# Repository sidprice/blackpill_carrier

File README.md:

# blackpill_carrier

This PCB is to be used to make a stable Blackmagic Probe debugger when the platform is Blackpill, in particular the F411 blackpill.

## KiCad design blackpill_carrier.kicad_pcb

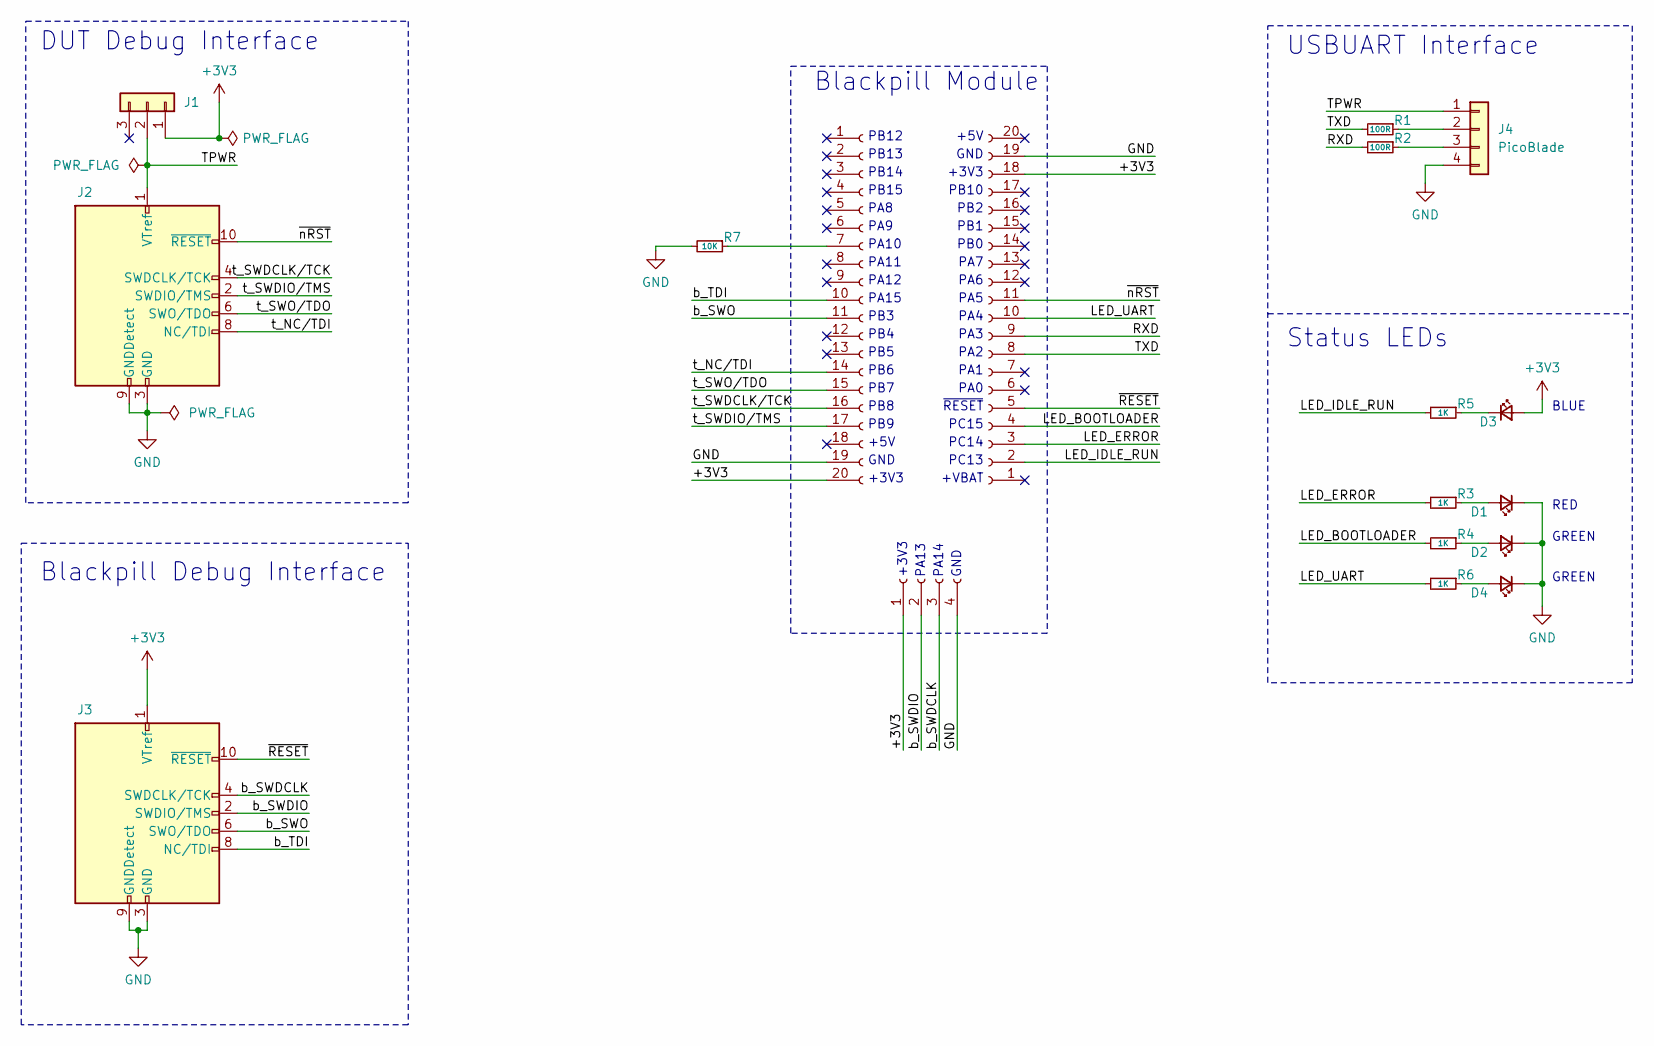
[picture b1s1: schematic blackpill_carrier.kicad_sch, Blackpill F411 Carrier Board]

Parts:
D1: LTSTC170KR; LTSTC170_LED_0805; LCSC C94868
D2, D4: LTSTC170KG; LTSTC170_LED_0805; LCSC C98221
D3: LTSTC170KB; LTSTC170_LED_0805; LCSC C98222
J1: M50-3630342; PinHeader_1x03_P1.27mm_Vertical_SMD_Pin1Right; LCSC C3336318
J2, J3: FTSH-105-01-F-DV-K-P-TR; PinHeader_2x05_P1.27mm_Vertical_SMD; Mouser 200-FTSH10501FDVKPTR
J4: PicoBlade; Molex_PicoBlade_53261-0471_1x04-1MP_P1.25mm_Horizontal; Mouser 538-53261-0471
J5, J6: B-2200S20P-A120; PinSocket_1x20_P2.54mm_Vertical; LCSC C124410
J7: B-2200S04P-A120; PinSocket_1x04_P2.54mm_Vertical; LCSC C124413
R1, R2: 100R; R_0603_1608Metric; LCSC C25201
R3, R4, R5, R6: 1K; R_0603_1608Metric; LCSC C25585
R7: 10K; R_0603_1608Metric; LCSC C15401

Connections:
+3V3: D3.2 (A), J1.1, J3.1 (VTref), J5.20, J6.18, J7.1
/LED_BOOTLOADER: J6.4, R4.2
/LED_ERROR: J6.3, R3.2
/LED_IDLE_RUN: J6.2, R5.2
/LED_UART: J6.10, R6.2
/RXD: J6.9, R2.2
/TPWR: J1.2, J2.1 (VTref), J4.1
/TXD: J6.8, R1.2
/b_SWDCLK: J3.4 (SWDCLK/TCK), J7.3
/b_SWDIO: J3.2 (SWDIO/TMS), J7.2
/b_SWO: J3.6 (SWO/TDO), J5.11
/b_TDI: J3.8 (NC/TDI), J5.10
/t_NC/TDI: J2.8 (NC/TDI), J5.14
/t_SWDCLK/TCK: J2.4 (SWDCLK/TCK), J5.16
/t_SWDIO/TMS: J2.2 (SWDIO/TMS), J5.17
/t_SWO/TDO: J2.6 (SWO/TDO), J5.15
/~RESET: J3.10 (~RESET), J6.5
/~nRST: J2.10 (~RESET), J6.11
GND: D1.1 (K), D2.1 (K), D4.1 (K), J2.3 (GND), J2.5 (GND), J2.9 (GNDDetect), J3.3 (GND), J3.5 (GND), J3.9 (GNDDetect), J4.4, J5.19, J6.19, J7.4, R7.2
unnamed: D1.2 (A), R3.1
unnamed: D2.2 (A), R4.1
unnamed: D3.1 (K), R5.1
unnamed: D4.2 (A), R6.1
unnamed: J4.2, R1.1
unnamed: J4.3, R2.1
unnamed: J5.7, R7.1

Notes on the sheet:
PB6
GND
PA4
PB3
PB2
USBUART Interface
PB12
PA15
PA0
RED
+3V3
PB14
PA13
PA14
GREEN
PB1
PB7
PB9
PA12
+VBAT
PA1
PC14
PA5
PA11
PA3
PA8
~{RESET}
PA9
DUT Debug Interface
PA10
PB13
PC13
PB10
PC15
PB5
+5V
Blackpill Debug Interface
PA6
PB8
BLUE

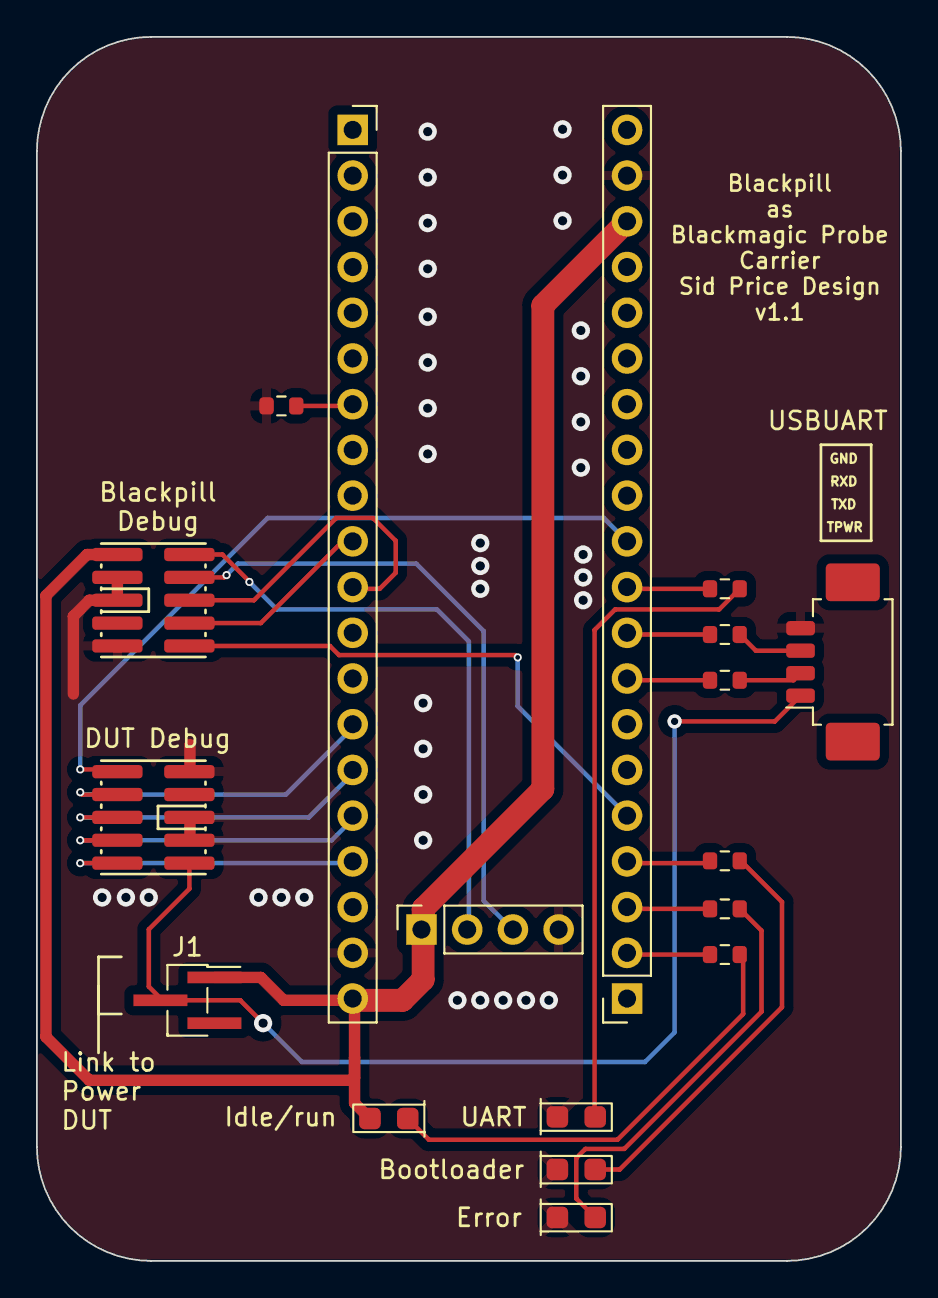
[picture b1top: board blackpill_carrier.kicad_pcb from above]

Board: 2 copper layers, 48.0 x 68.0 mm, 18 parts (0 on the bottom side), 26 nets.

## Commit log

2024-08-16 V1.0 PCB
2024-08-16 Short comment added to Readme
2024-08-24 Partial BOM updates for LCSC part numbers
    The Picoblade and the Blackpill need addressing. For the Blackpill, need to switch to using a set of SMT headers (to reduce assembly cost).
2024-08-24 Update .gitignore to exclude some generated files
2024-08-25 Initial layout and component updates
    May require more work after testing is completed
2024-08-27 Remove test points etc.
    Removed all components not REQUIRED for BMF to operate.
    Also removed unwanted jumper.
    Changed footprint of target power selector.
    Added pull-down for PA10
2024-08-27 Ignore the PCBWay folder
    Don't need to track generated files.
2024-08-28 Update 3D model for connector and fix silkscreen
2024-09-18 Reduce size and re-arrange layout to look better.
2024-10-03 Updates for PCBWay
